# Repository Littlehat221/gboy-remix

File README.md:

# gboy-remix
Remix of gmanmodz's gboy rev 3

All gerbers require 4LayerTech boards: may make new boards in the future to remove reliance.

Includes .stl files, gerbers, and a BOM
Included are KICAD files so anyone can edit them for their own project, as well as some footprints and symbols used to create mine.
Also inclued are fusion files for easy editing. No more .stl conversions.

BOM links are probably going to die.

TODO:
- include BOM
- .f3d files
- new PCB not using 4layertech boards

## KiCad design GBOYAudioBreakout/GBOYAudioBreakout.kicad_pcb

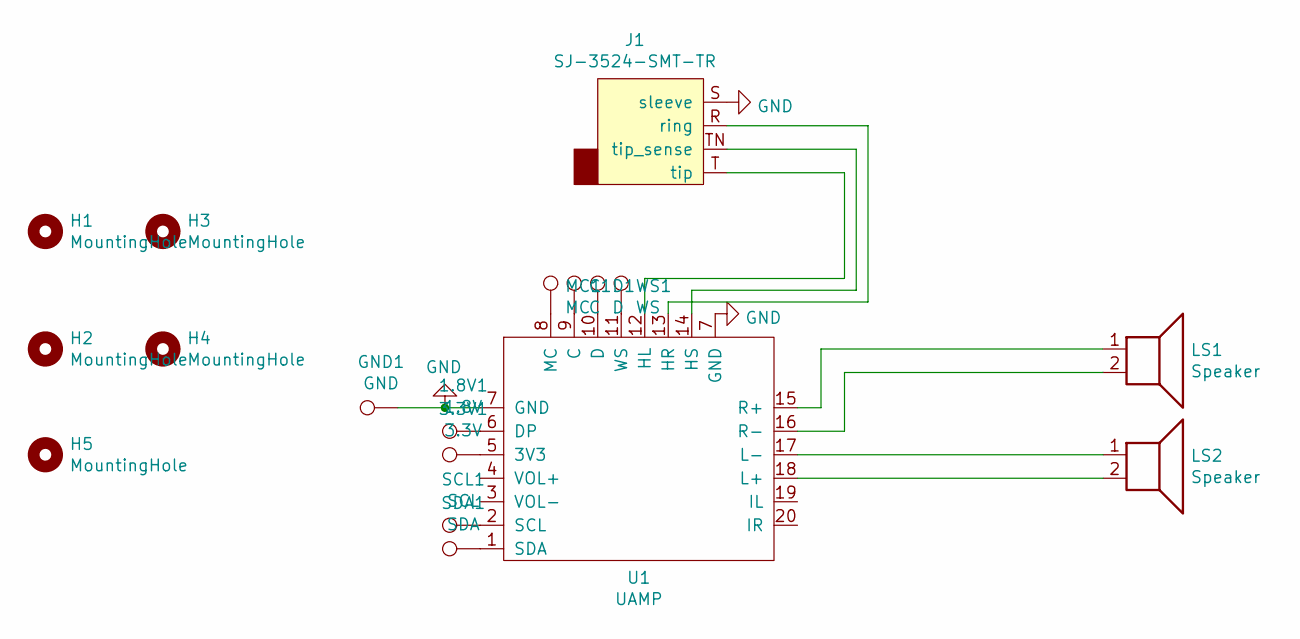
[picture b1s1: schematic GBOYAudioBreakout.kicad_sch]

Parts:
1.8V1: 1.8V; TestPoint_Pad_D1.5mm
3.3V1: 3.3V; TestPoint_Pad_D1.5mm
C1: C; TestPoint_Pad_D1.5mm
D1: D; TestPoint_Pad_D1.5mm
GND1: GND; TestPoint_Pad_D1.5mm
H1, H2, H3, H4, H5: MountingHole; MountingHole_2.2mm_M2
J1: SJ-3524-SMT-TR; Jack_3.5mm_CUI_SJ-3524-SMT_Horizontal
LS1, LS2: Speaker; SP-1511S-3
MC1: MC; TestPoint_Pad_D1.5mm
SCL1: SCL; TestPoint_Pad_D1.5mm
SDA1: SDA; TestPoint_Pad_D1.5mm
U1: UAMP; UAMP2
WS1: WS; TestPoint_Pad_D1.5mm

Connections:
GND: GND1.1, J1.S (sleeve), U1.7 (GND)
unnamed: 1.8V1.1, U1.6 (DP)
unnamed: 3.3V1.1, U1.5 (3V3)
unnamed: C1.1, U1.9 (C)
unnamed: D1.1, U1.10 (D)
unnamed: J1.T (tip), U1.12 (HL)
unnamed: J1.TN (tip_sense), U1.14 (HS)
unnamed: LS1.1, U1.15 (R+)
unnamed: LS1.2, U1.16 (R-)
unnamed: LS2.1, U1.17 (L-)
unnamed: LS2.2, U1.18 (L+)
unnamed: MC1.1, U1.8 (MC)
unnamed: SCL1.1, U1.2 (SCL)
unnamed: SDA1.1, U1.1 (SDA)
unnamed: U1.11 (WS), WS1.1
unnamed: J1.R (ring), U1.13 (HR)

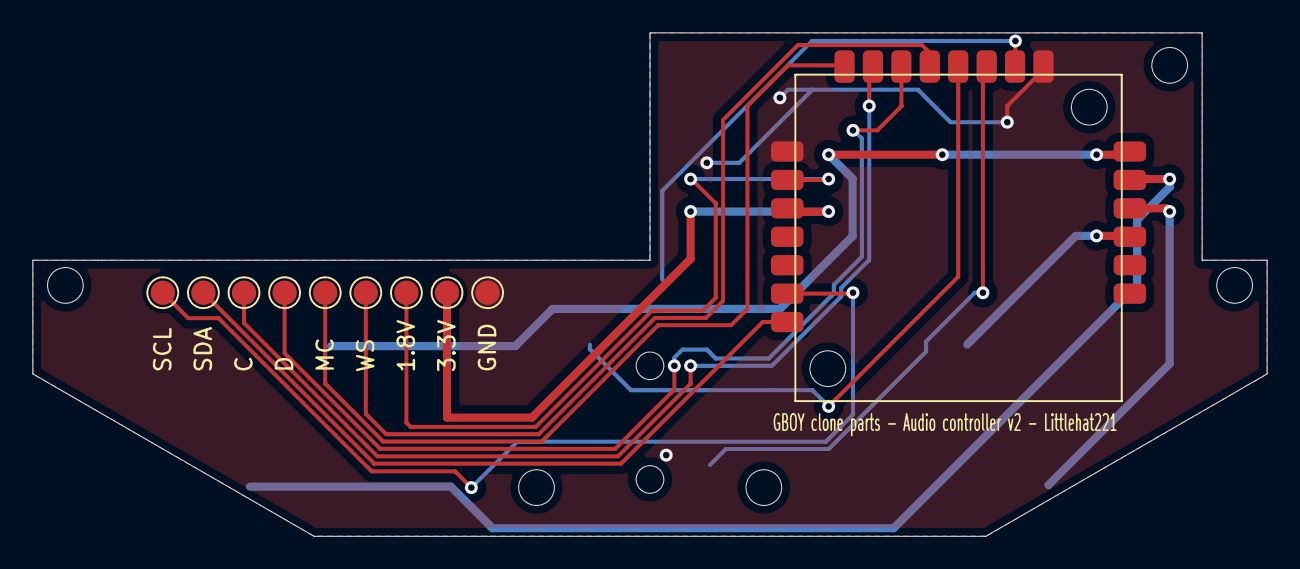
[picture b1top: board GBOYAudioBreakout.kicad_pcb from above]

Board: 2 copper layers, 76.0 x 31.0 mm, 18 parts (1 on the bottom side), 16 nets.

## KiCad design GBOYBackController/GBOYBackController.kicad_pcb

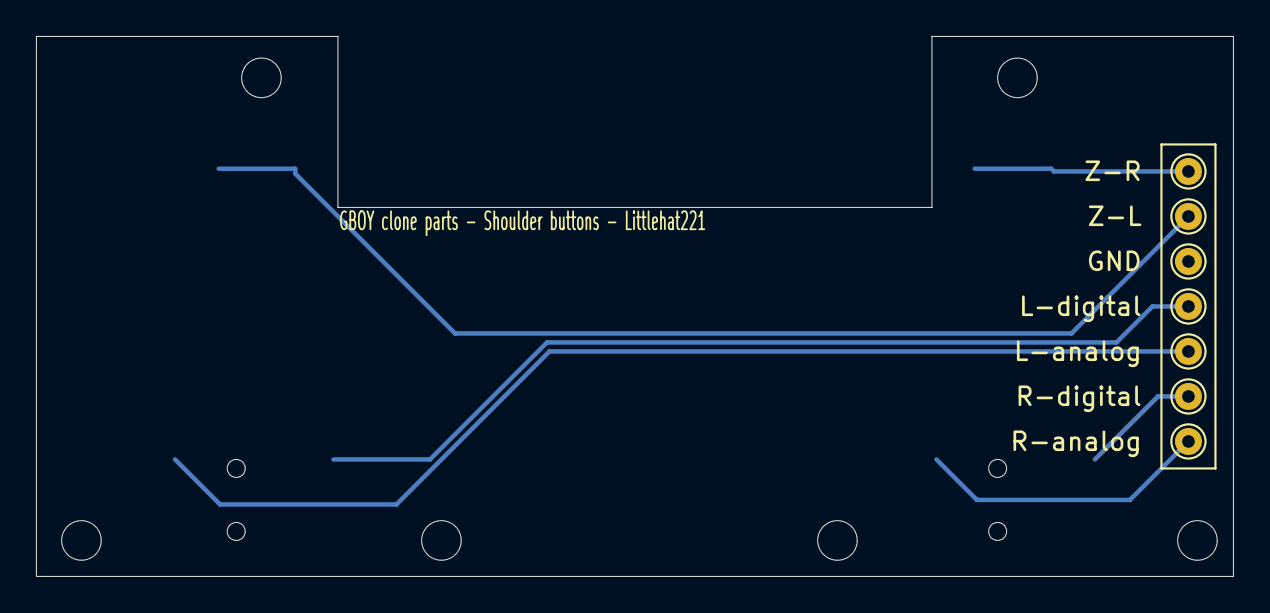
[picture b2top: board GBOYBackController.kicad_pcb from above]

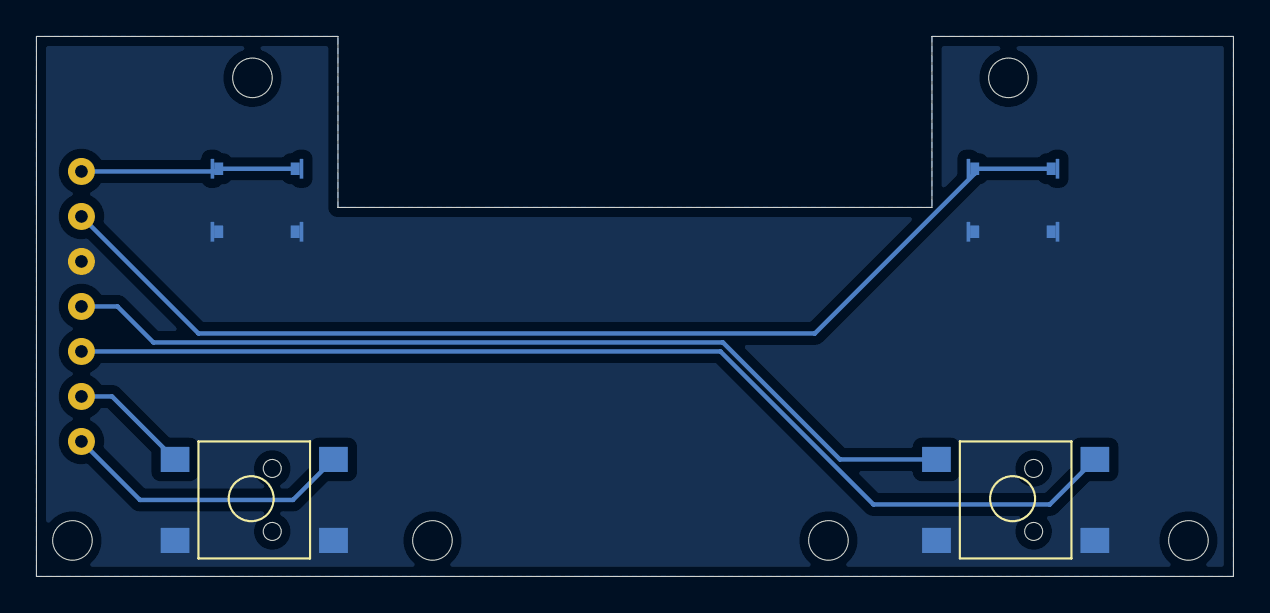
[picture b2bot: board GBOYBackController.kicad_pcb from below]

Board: 2 copper layers, 66.5 x 30.0 mm, 17 parts (4 on the bottom side), 7 nets.

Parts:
H1, H2, H3, H5, H6, H7: MountingHole; MountingHole_2.2mm_M2
SW2, SW4: TMHF07
TP1: R-analog; TestPoint_THTPad_D1.5mm_Drill0.7mm
TP2: R-digital; TestPoint_THTPad_D1.5mm_Drill0.7mm
TP3: L-analog; TestPoint_THTPad_D1.5mm_Drill0.7mm
TP4: L-digital; TestPoint_THTPad_D1.5mm_Drill0.7mm
TP5: Z-L; TestPoint_THTPad_D1.5mm_Drill0.7mm
TP6: Z-R; TestPoint_THTPad_D1.5mm_Drill0.7mm
TP7: GND; TestPoint_THTPad_D1.5mm_Drill0.7mm
U1, U2: TL3315NF

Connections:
GND: SW2.C, SW2.D, SW4.C, SW4.D, TP7.1, U1.1, U1.2, U2.1, U2.2
unnamed: SW2.1, TP4.1
unnamed: SW2.2, TP3.1
unnamed: SW4.1, TP2.1
unnamed: SW4.2, TP1.1
unnamed: TP5.1, U1.3, U1.4
unnamed: TP6.1, U2.3, U2.4

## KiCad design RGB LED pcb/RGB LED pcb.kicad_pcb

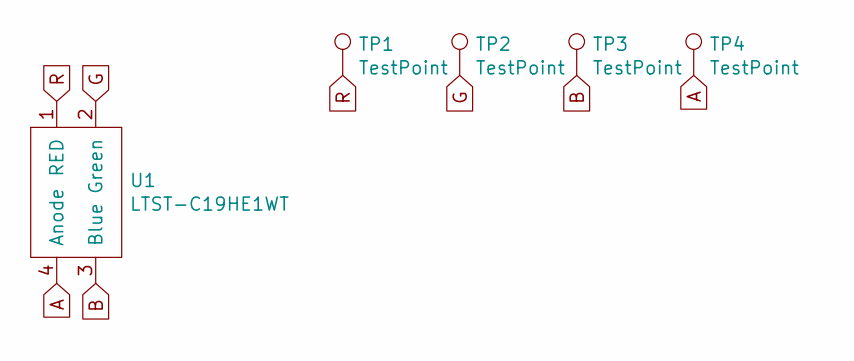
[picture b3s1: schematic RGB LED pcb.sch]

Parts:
TP1, TP2, TP3, TP4: TestPoint; 1.25mm pad
U1: LTST-C19HE1WT

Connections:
A: TP4.1, U1.4 (Anode)
B: TP3.1, U1.3 (Blue)
G: TP2.1, U1.2 (Green)
R: TP1.1, U1.1 (RED)

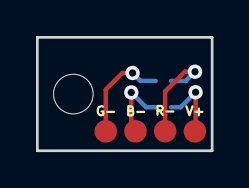
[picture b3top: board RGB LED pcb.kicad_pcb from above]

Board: 2 copper layers, 9.7 x 6.3 mm, 5 parts (1 on the bottom side), 4 nets.

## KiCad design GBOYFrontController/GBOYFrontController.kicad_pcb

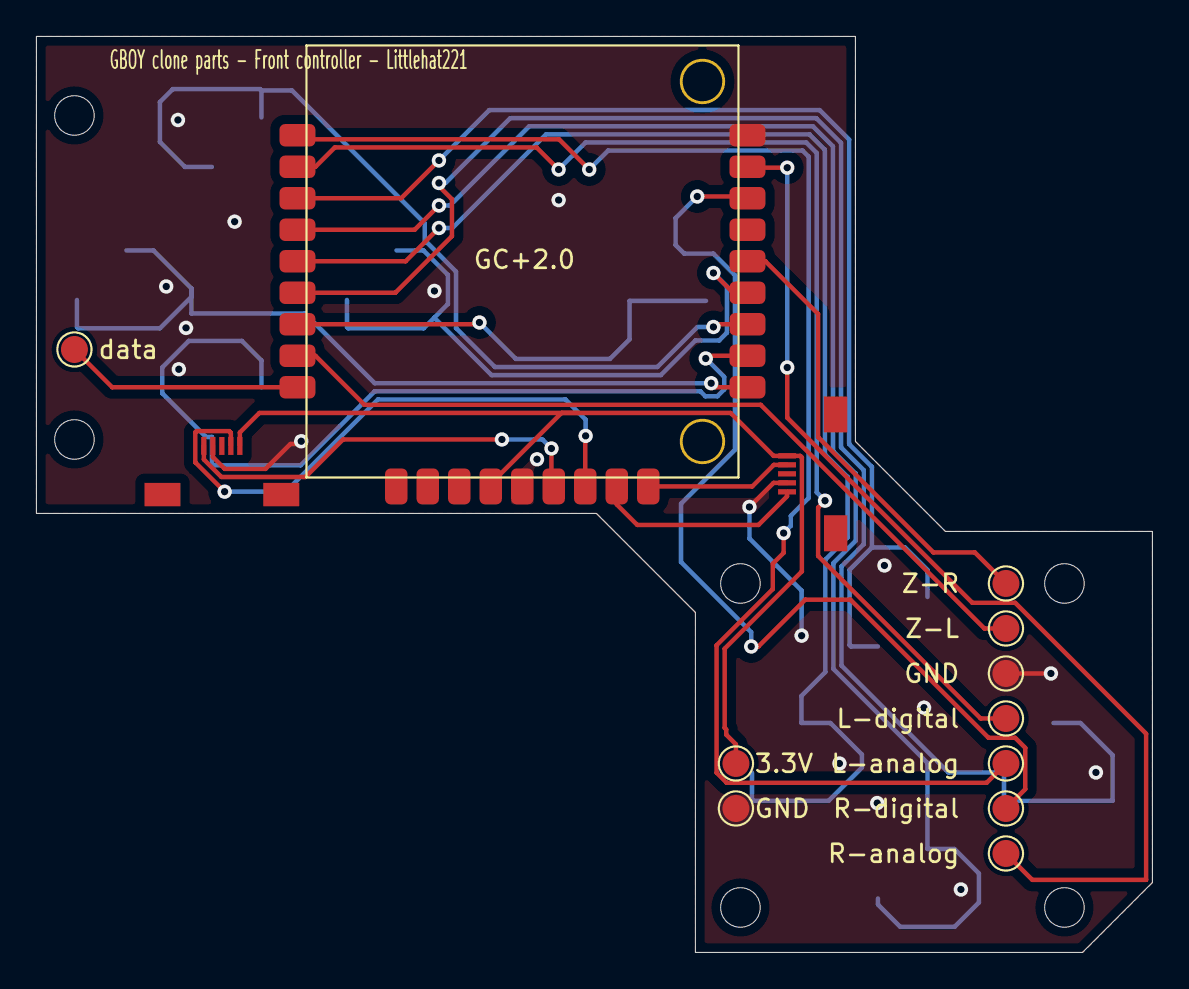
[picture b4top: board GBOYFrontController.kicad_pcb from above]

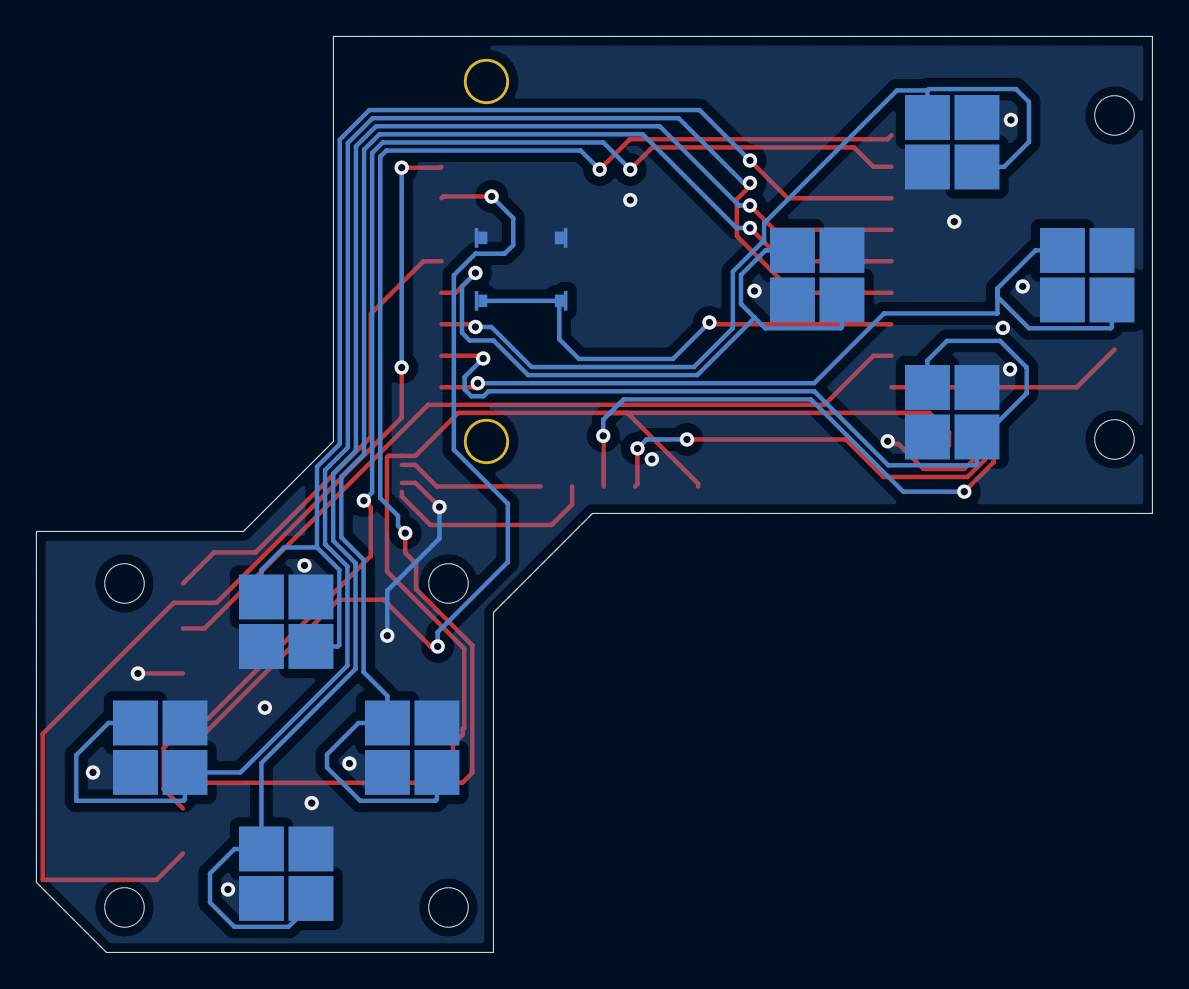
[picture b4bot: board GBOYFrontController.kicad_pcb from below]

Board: 2 copper layers, 62.0 x 50.9 mm, 28 parts (9 on the bottom side), 22 nets.

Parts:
H1, H2, H3, H4, H5, H6: MountingHole; MountingHole_2.2mm_M2
J1: left_stick; 5051100592
J2: right_stick; 5051100592
TP1: data; TestPoint_Pad_D1.5mm
TP2: R-analog; TestPoint_Pad_D1.5mm
TP3: R-digital; TestPoint_Pad_D1.5mm
TP4: L-analog; TestPoint_Pad_D1.5mm
TP5: L-digital; TestPoint_Pad_D1.5mm
TP6: Z-L; TestPoint_Pad_D1.5mm
TP7: Z-R; TestPoint_Pad_D1.5mm
TP8, TP9: GND; TestPoint_Pad_D1.5mm
TP10: 3.3V; TestPoint_Pad_D1.5mm
U1: GC+2.0; GC+2.0 - GOBY
U2, U3, U4, U5, U6, U7, U8, U9: copper_pad_button; copper contact button
U10: TL3315NF

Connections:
3.3v: J1.5, J2.5, TP10.1, U1.10
A: U1.1, U9.1, U9.4
B: U1.2, U8.1, U8.4
D: U1.15, U4.1, U4.4
GND: J1.2, J2.2, TP8.1, TP9.1, U1.9, U2.2, U2.3, U3.2, U3.3, U4.2, U4.3, U5.2, U5.3, U6.2, U6.3, U7.2, U7.3, U8.2, U8.3, U9.2, U9.3, U10.3, U10.4
L: U1.17, U2.1, U2.4
unnamed: J1.1, U1.26
unnamed: J1.4, U1.27
unnamed: J2.1, U1.24
unnamed: J2.4, U1.25
unnamed: TP1.1, U1.20
unnamed: TP2.1, U1.8
unnamed: TP3.1, U1.7
unnamed: TP4.1, U1.12
unnamed: TP5.1, U1.13
unnamed: TP6.1, U1.19
unnamed: TP7.1, U1.5
R: U1.16, U5.1, U5.4
S: U1.18, U10.1, U10.2
U: U1.14, U3.1, U3.4
X: U1.3, U7.1, U7.4
Y: U1.4, U6.1, U6.4

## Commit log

2022-11-21 Added PCBs
    Included GBOY Front, Back, and Audio boards.
2022-11-21 rename
